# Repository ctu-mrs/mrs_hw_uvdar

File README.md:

# UVDAR Hardware

## Description
This package contains hardware for UVDAR.<br>
[UVDAR](https://github.com/ctu-mrs/uvdar_core) Hardware is available in two variants: standalone and as MRS Module.<br>

The standalone variant can be connected to a computer directly using USB and is intended for quick development and trying out UVDAR.<br>
The MRS Module variant is intended to be used along with MRS Distribution Boards, namely with F450 Distribution Board as this is so far the
only Distribution board populated with a slot for a Big MRS Module.

<table>
  <tr>
    <th>
      UVDAR Standalone Variant
    </th>
    <th>
      UVDAR Module Variant
    </th>
  </tr>
  <tr>
    <td>
      
    </td>
    <td>
      
    </td>
  </tr>
</table>

## How to use
1) Read the documentation provided with each variant.
2) Select which variant suits your needs better (note that you can use MRS Module Host Board for development with MRS Module variant).
3) Manufacture and assemble the PCB of the controller and the UV LEDs. The Gerber files as well as BOM is in the PCB folder of each variant.
4) Flash the control board with appropriate firmware using STM32CubeIDE, Atollic TrueSTUDIO, Keil uVision or STM32CubePRogrammer or any other software you like to use.
5) Connect the controller to a computer and use the [UVDAR ROS Package](https://github.com/ctu-mrs/uvdar_core).

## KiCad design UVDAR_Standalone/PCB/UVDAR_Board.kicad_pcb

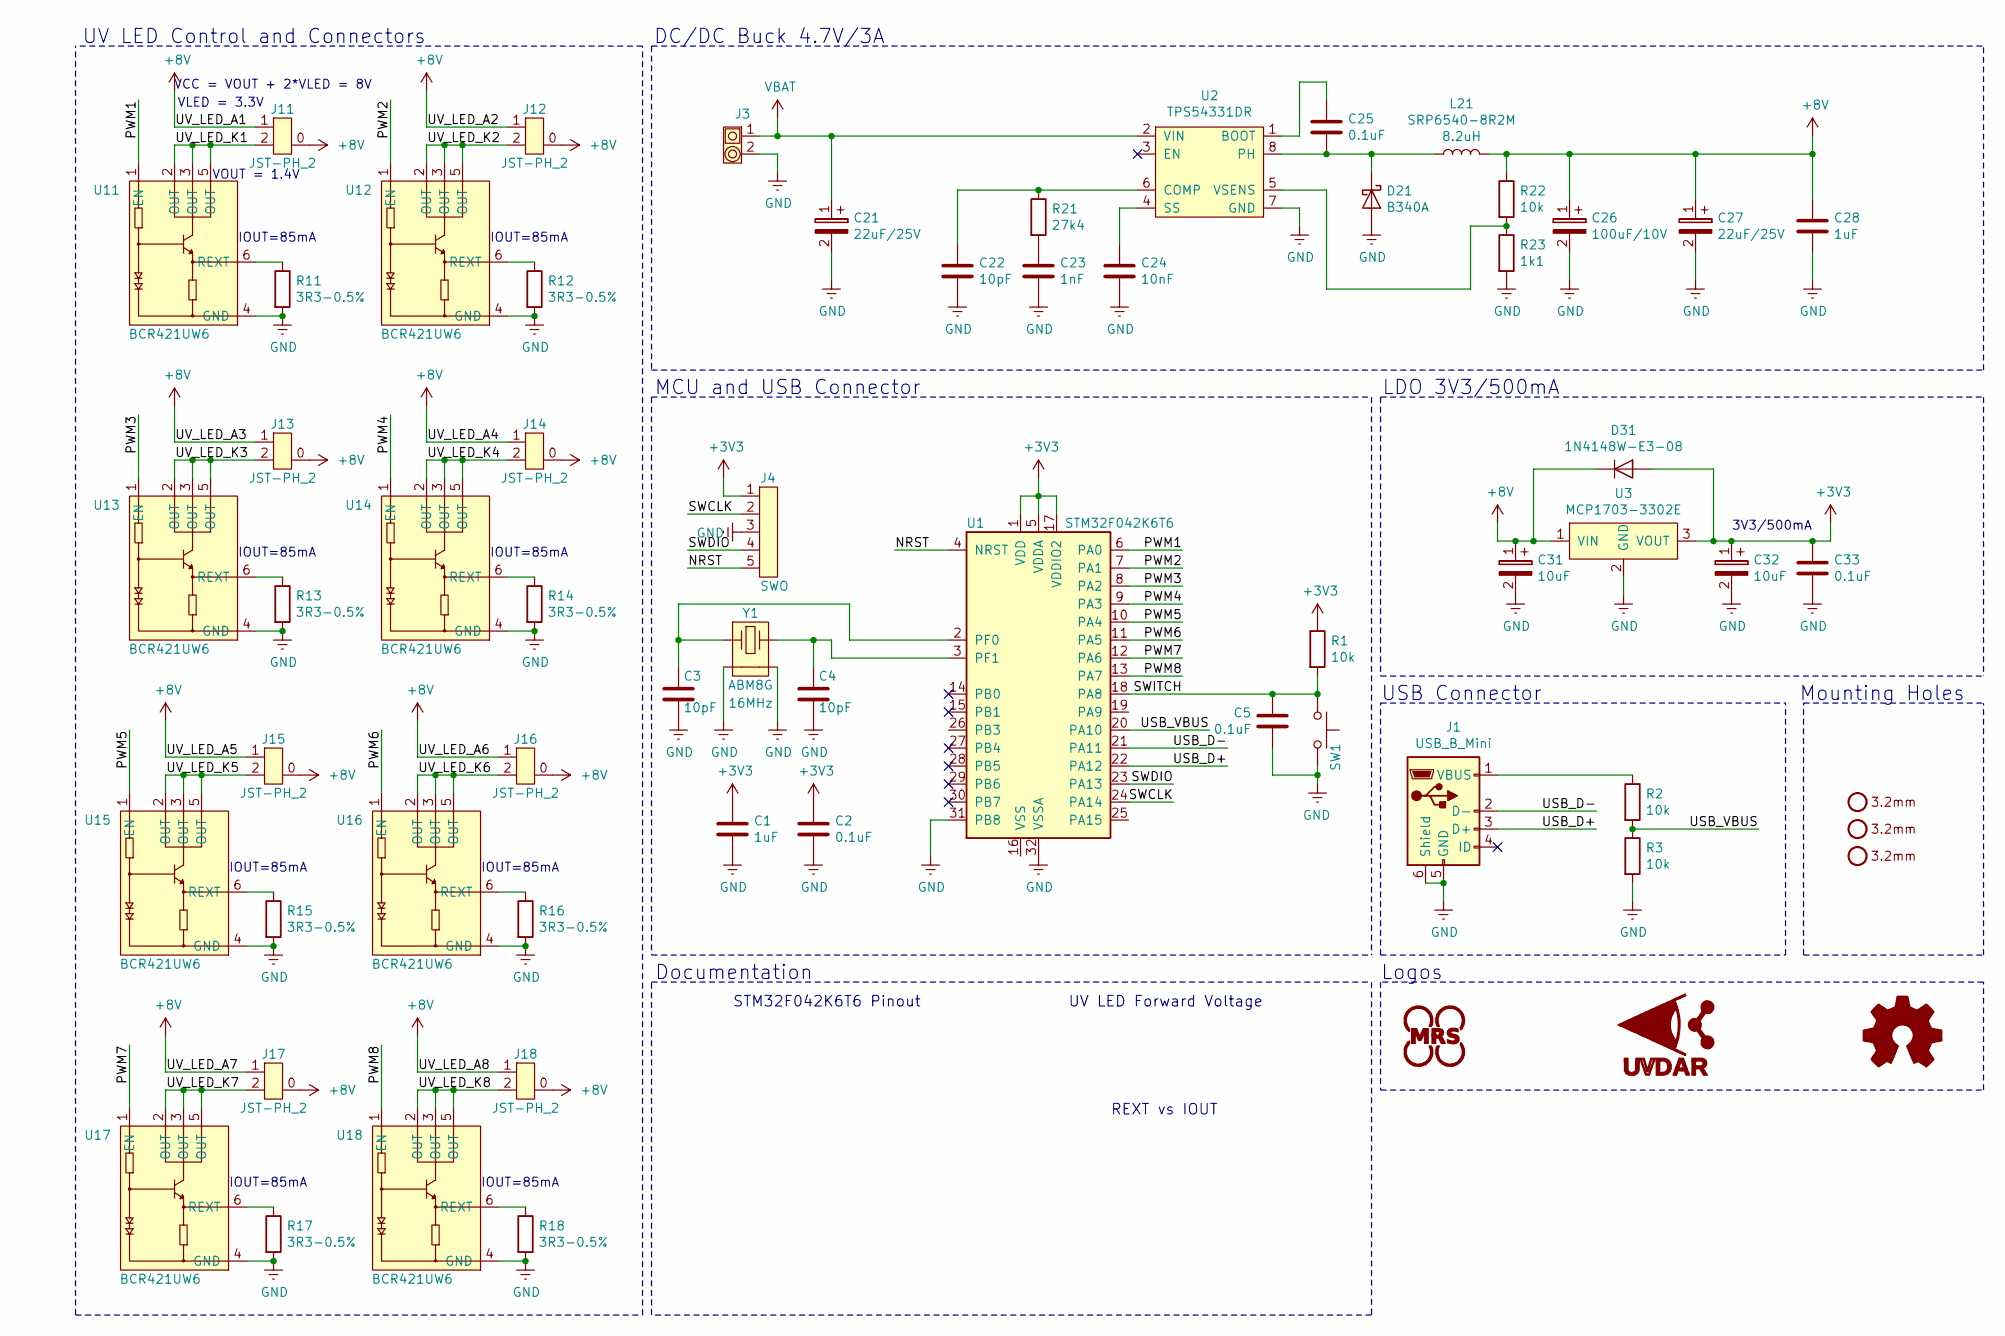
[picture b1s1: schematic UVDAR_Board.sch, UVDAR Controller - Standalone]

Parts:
C1, C28: 1uF; C0603; Farnell 2533943
C2, C5, C25, C33: 0.1uF; C0603; Farnell 2821272
C3, C4, C22: 10pF; C0603; Mouser 710-885012006051
C21, C27: 22uF/25V; CTAN2412; Farnell 2353066
C23: 1nF; C0603; Farnell 2534019
C24: 10nF; C0603; Farnell 1759102
C26: 100uF/10V; CTAN2312; Farnell 197180
C31, C32: 10uF; CTAN1206; Farnell 197130
D21: B340A; D_SMA; Farnell 2335183
D31: 1N4148W-E3-08; SOD-123; Farnell 2433353
H1, H2, H3: Mounting_hole_unplated_3,2mm
J1: USB_B_Mini; USB_Mini-B_Lumberg_2486_01_Horizontal; Farnell 1243250
J3: Power_Input; power_connector_small
J4: SWO; Header_1x05_P2.54mm
J11, J12, J13, J14, J15, J16, J17, J18: JST-PH_2; JST_PH_2; Mouser X
L21: SRP6540-8R2M; L_SRP6540; Farnell 2309903
LOGO1: MRS_Logo; MRS_10mm
LOGO2: UVDAR_Logo; UVDAR_7mm
LOGO3: Logo_Open_Hardware_Small; OSHW-Logo2_7.3x6mm_SilkScreen
R1, R2, R3, R22: 10k; R0603; Mouser 71-CRCW0603-10K-E3
R11, R12, R13, R14, R15, R16, R17, R18: 3R3-0.5%; R0603; Farnell 2447365
R21: 27k4; R0603; Mouser 652-CR0603FX-2742ELF
R23: 1k1; R0603; Mouser *
SW1: Push-Switch_SMT_6x6mm; Tactile_Switch_6x6_SMT; Farnell 2320087
U1: STM32F042K6T6; LQFP-32_7x7mm_P0.8mm; Farnell 2750629
U2: TPS54331DR; SOIC-8; Farnell 2781730
U3: MCP1703-3302E; SOT-223-3(TAB-pin-2); Farnell *
U11, U12, U13, U14, U15, U16, U17, U18: BCR421UW6; SOT-26-6; Mouser 621-BCR421UW6-7
Y1: ABM8G; Farnell 2467841

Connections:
+3V3: C1.1, C2.1, C32.1, C33.1, D31.2 (A), J4.1, R1.1, U1.1 (VDD), U1.5 (VDDA), U1.17 (VDDIO2), U3.3 (VOUT)
+8V: C26.1, C27.1, C28.1, C31.1, D31.1 (K), J11.0, J11.1, J12.0, J12.1, J13.0, J13.1, J14.0, J14.1, J15.0, J15.1, J16.0, J16.1, J17.0, J17.1, J18.0, J18.1, L21.2, R22.1, U3.1 (VIN)
/NRST: J4.5, U1.4 (NRST)
/PWM1: U1.6 (PA0), U11.1 (EN)
/PWM2: U1.7 (PA1), U12.1 (EN)
/PWM3: U1.8 (PA2), U13.1 (EN)
/PWM4: U1.9 (PA3), U14.1 (EN)
/PWM5: U1.10 (PA4), U15.1 (EN)
/PWM6: U1.11 (PA5), U16.1 (EN)
/PWM7: U1.12 (PA6), U17.1 (EN)
/PWM8: U1.13 (PA7), U18.1 (EN)
/SWCLK: J4.2, U1.24 (PA14)
/SWDIO: J4.4, U1.23 (PA13)
/SWITCH: C5.1, R1.2, SW1.2, U1.18 (PA8)
/USB_D+: J1.3 (D+), U1.22 (PA12)
/USB_D-: J1.2 (D-), U1.21 (PA11)
/USB_VBUS: R2.2, R3.1, U1.20 (PA10)
/UV_LED_K1: J11.2, U11.2 (OUT), U11.3 (OUT), U11.5 (OUT)
/UV_LED_K2: J12.2, U12.2 (OUT), U12.3 (OUT), U12.5 (OUT)
/UV_LED_K3: J13.2, U13.2 (OUT), U13.3 (OUT), U13.5 (OUT)
/UV_LED_K4: J14.2, U14.2 (OUT), U14.3 (OUT), U14.5 (OUT)
/UV_LED_K5: J15.2, U15.2 (OUT), U15.3 (OUT), U15.5 (OUT)
/UV_LED_K6: J16.2, U16.2 (OUT), U16.3 (OUT), U16.5 (OUT)
/UV_LED_K7: J17.2, U17.2 (OUT), U17.3 (OUT), U17.5 (OUT)
/UV_LED_K8: J18.2, U18.2 (OUT), U18.3 (OUT), U18.5 (OUT)
GND: C1.2, C2.2, C3.2, C4.2, C5.2, C21.2, C22.2, C23.2, C24.2, C26.2, C27.2, C28.2, C31.2, C32.2, C33.2, D21.2 (A), J1.5 (GND), J1.6 (Shield), J3.2, J4.3, R3.2, R11.2, R12.2, R13.2, R14.2, R15.2, R16.2, R17.2, R18.2, R23.2, SW1.1, U1.31 (PB8), U1.32 (VSSA), U2.7 (GND), U3.2 (GND), U11.4 (GND), U12.4 (GND), U13.4 (GND), U14.4 (GND), U15.4 (GND), U16.4 (GND), U17.4 (GND), U18.4 (GND), Y1.2, Y1.4
unnamed: C3.1, U1.2 (PF0), Y1.1
unnamed: C4.1, U1.3 (PF1), Y1.3
unnamed: C22.1, R21.1, U2.6 (COMP)
unnamed: C23.1, R21.2
unnamed: C24.1, U2.4 (SS)
unnamed: C25.1, U2.1 (BOOT)
unnamed: C25.2, D21.1 (K), L21.1, U2.8 (PH)
unnamed: J1.1 (VBUS), R2.1
unnamed: R11.1, U11.6 (REXT)
unnamed: R12.1, U12.6 (REXT)
unnamed: R13.1, U13.6 (REXT)
unnamed: R14.1, U14.6 (REXT)
unnamed: R15.1, U15.6 (REXT)
unnamed: R16.1, U16.6 (REXT)
unnamed: R17.1, U17.6 (REXT)
unnamed: R18.1, U18.6 (REXT)
unnamed: R22.2, R23.1, U2.5 (VSENS)
VBAT: C21.1, J3.1, U2.2 (VIN)

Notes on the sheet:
VOUT = 1.4V
VCC = VOUT + 2*VLED = 8V
VLED = 3.3V
UV LED Forward Voltage
STM32F042K6T6 Pinout
REXT vs IOUT
IOUT=85mA
UV LED Control and Connectors
Documentation
MCU and USB Connector
3V3/500mA
LDO 3V3/500mA
DC/DC Buck 4.7V/3A
USB Connector
Mounting Holes
Logos

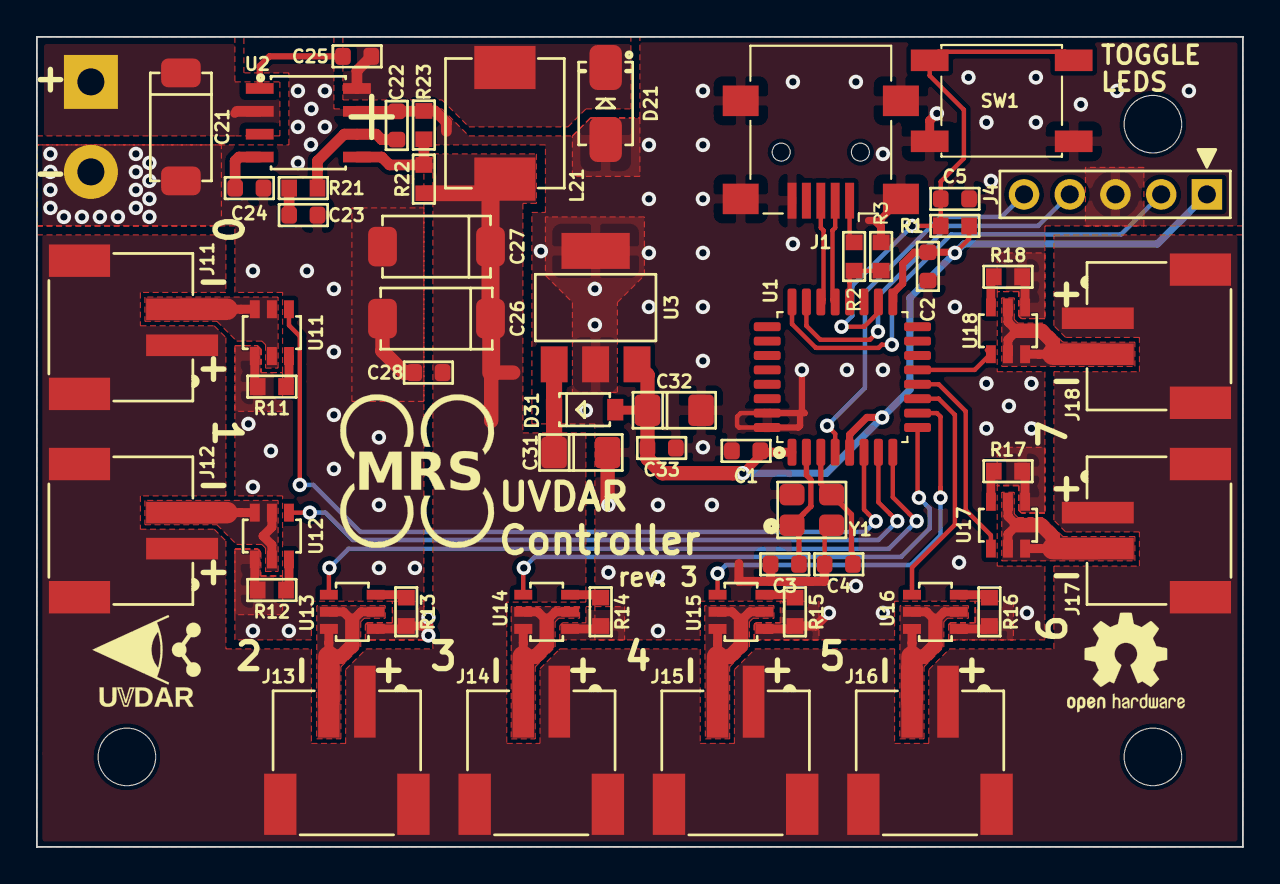
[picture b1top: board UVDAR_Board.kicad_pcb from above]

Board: 2 copper layers, 67.0 x 45.0 mm, 63 parts (0 on the bottom side), 44 nets.

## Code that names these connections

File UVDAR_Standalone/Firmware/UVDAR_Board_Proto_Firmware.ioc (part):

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Mcu.Name=STM32F042K(4-6)Tx
Mcu.Package=LQFP32
Mcu.UserName=STM32F042K6Tx
PA0.GPIOParameters=GPIO_Speed,GPIO_Label
PA0.GPIO_Label=UV_LED_0
PA0.GPIO_Speed=GPIO_SPEED_FREQ_HIGH
PA0.Signal=GPIO_Output
PA1.GPIOParameters=GPIO_Speed,GPIO_Label
PA1.GPIO_Label=UV_LED_1
PA1.GPIO_Speed=GPIO_SPEED_FREQ_HIGH
PA1.Signal=GPIO_Output
PA10.GPIOParameters=GPIO_Label,GPIO_ModeDefaultEXTI
PA10.GPIO_Label=USB_VBUS
PA10.GPIO_ModeDefaultEXTI=GPIO_MODE_IT_RISING_FALLING
PA10.Signal=GPXTI10
PA11.Mode=Device
PA11.Signal=USB_DM
PA12.Mode=Device
PA12.Signal=USB_DP
PA13.Mode=Serial_Wire
PA13.Signal=SYS_SWDIO
PA14.Mode=Serial_Wire
PA14.Signal=SYS_SWCLK
PA2.GPIOParameters=GPIO_Speed,GPIO_Label
PA2.GPIO_Label=UV_LED_2
PA2.GPIO_Speed=GPIO_SPEED_FREQ_HIGH
PA2.Signal=GPIO_Output
PA3.GPIOParameters=GPIO_Speed,GPIO_Label
PA3.GPIO_Label=UV_LED_3
PA3.GPIO_Speed=GPIO_SPEED_FREQ_HIGH
PA3.Signal=GPIO_Output
PA4.GPIOParameters=GPIO_Speed,GPIO_Label
PA4.GPIO_Label=UV_LED_4
PA4.GPIO_Speed=GPIO_SPEED_FREQ_HIGH
PA4.Signal=GPIO_Output
PA5.GPIOParameters=GPIO_Speed,GPIO_Label
PA5.GPIO_Label=UV_LED_5
PA5.GPIO_Speed=GPIO_SPEED_FREQ_HIGH
PA5.Signal=GPIO_Output
PA6.GPIOParameters=GPIO_Speed,GPIO_Label
PA6.GPIO_Label=UV_LED_6
PA6.GPIO_Speed=GPIO_SPEED_FREQ_HIGH
PA6.Signal=GPIO_Output
PA7.GPIOParameters=GPIO_Speed,GPIO_Label
PA7.GPIO_Label=UV_LED_7
PA7.GPIO_Speed=GPIO_SPEED_FREQ_HIGH
PA7.Signal=GPIO_Output
PA8.GPIOParameters=GPIO_Label
PA8.GPIO_Label=SWITCH
PA8.Signal=GPXTI8
PF0-OSC_IN.Mode=HSE-External-Oscillator
PF0-OSC_IN.Signal=RCC_OSC_IN
PF1-OSC_OUT.Mode=HSE-External-Oscillator
PF1-OSC_OUT.Signal=RCC_OSC_OUT
RCC.HSE_VALUE=16000000
RCC.SYSCLKFreq_VALUE=48000000
RCC.SYSCLKSource=RCC_SYSCLKSOURCE_HSI48
board=custom

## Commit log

2021-02-09 Added UVDAR Module PCB and Firmware.
2021-02-09 Edit README.
2021-02-10 Changed uv_led_counter from uint16_t to uint32_t.
2021-02-10 Added documentation.
2021-02-10 Updated README.
2021-02-10 Added UVDAR Standalone.
2021-02-22 Created (and tested) firmware for standalone UVDAR PCB.
